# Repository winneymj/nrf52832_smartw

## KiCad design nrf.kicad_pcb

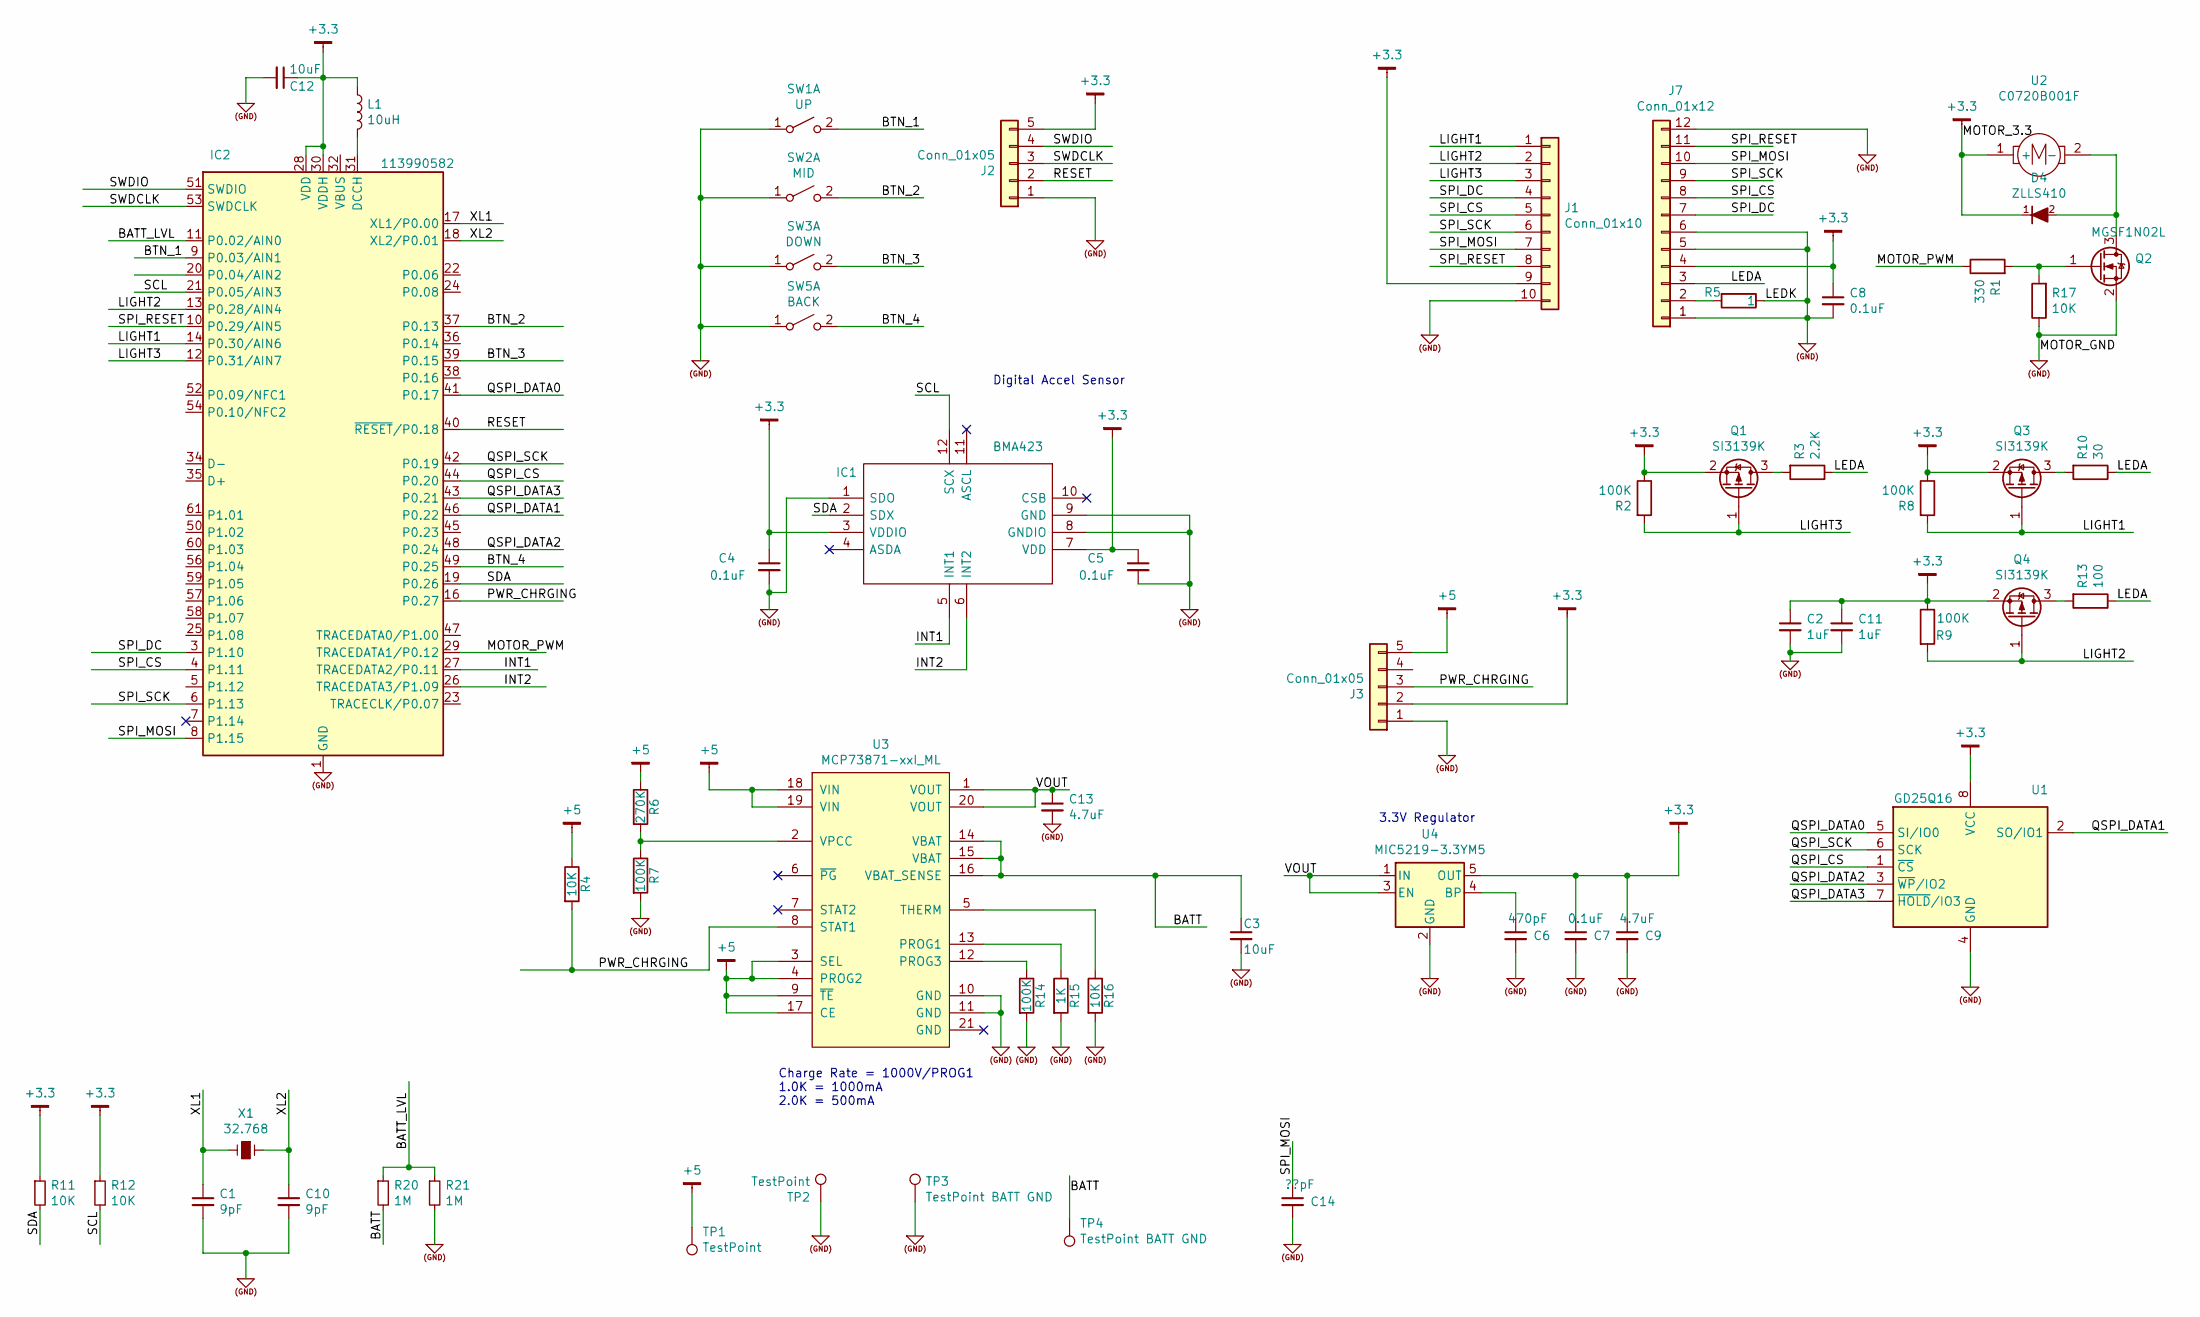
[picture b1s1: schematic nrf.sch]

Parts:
C1, C10: 9pF; C_0603_1608Metric_Pad1.08x0.95mm_HandSolder
C2, C11: 1uF; C_0603_1608Metric_Pad1.08x0.95mm_HandSolder
C3, C12: 10uF; C_0603_1608Metric_Pad1.08x0.95mm_HandSolder
C4, C5, C7, C8: 0.1uF; C_0603_1608Metric_Pad1.08x0.95mm_HandSolder
C6: 470pF; C_0603_1608Metric_Pad1.08x0.95mm_HandSolder
C9, C13: 4.7uF; C_0603_1608Metric_Pad1.08x0.95mm_HandSolder
C14: ??pF; C_0603_1608Metric_Pad1.08x0.95mm_HandSolder
D4: ZLLS410; D_SOD-323_HandSoldering
IC1: BMA423; LGA-12_2x2mm_P0.5mm_small_pad; Mouser Part Number 262-BMA423
IC2: 113990582; Raytac_MDBT50Q; Mouser Part Number 713-113990582
J1: Conn_01x10; Pin_Header_Straight_1x10_Pitch2.54mm
J2: Conn_01x05; Pin_Header_Straight_1x05_Pitch1.27mm
J3: Conn_01x05; Pin_Header_Straight_1x05_Pitch2.54mm
J7: Conn_01x12; FPC_12x0.7mm
L1: 10uH; L_0603_1608Metric_Pad1.05x0.95mm_HandSolder
Q1, Q3, Q4: SI3139K; SOT-723
Q2: MGSF1N02L; SOT-23
R1: 330; R_0603_1608Metric_Pad0.98x0.95mm_HandSolder
R2, R7, R8, R9, R14: 100K; R_0603_1608Metric_Pad0.98x0.95mm_HandSolder
R3: 2.2K; R_0603_1608Metric_Pad0.98x0.95mm_HandSolder
R4, R11, R12, R16, R17: 10K; R_0603_1608Metric_Pad0.98x0.95mm_HandSolder
R5: 1; R_0603_1608Metric_Pad0.98x0.95mm_HandSolder
R6: 270K; R_0603_1608Metric_Pad0.98x0.95mm_HandSolder
R10: 30; R_0603_1608Metric_Pad0.98x0.95mm_HandSolder
R13: 100; R_0603_1608Metric_Pad0.98x0.95mm_HandSolder
R15: 1K; R_0603_1608Metric_Pad0.98x0.95mm_HandSolder
R20, R21: 1M; R_0603_1608Metric_Pad0.98x0.95mm_HandSolder
SW1: UP; Tact_SW_3x6x3.5
SW2: MID; Tact_SW_3x6x3.5
SW3: DOWN; Tact_SW_3x6x3.5
SW5: BACK; Tact_SW_3x6x3.5
TP1, TP2: TestPoint; TestPoint_Pad_D1.5mm
TP3, TP4: TestPoint BATT GND; TestPoint_Pad_2.0x2.0mm
U1: GD25Q16; USON8-4x3
U2: C0720B001F; VIBRATION MOTOR COIN 3V FLEX - C0720B001F
U3: MCP73871-xxI_ML; QFN-20-1EP_4x4mm_Pitch0.5mm; MPN MCP73871-{output}I/ML
U4: MIC5219-3.3YM5; SOT-23-5
X1: 32.768; Crystal_SMD_EuroQuartz_EQ161-2pin_3.2x1.5mm_HandSoldering

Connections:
(GND): C1.2, C2.2, C3.2, C4.2, C5.2, C6.2, C7.2, C8.2, C9.2, C10.2, C11.2, C12.2, C13.2, C14.2, IC1.1 (SDO), IC1.8 (GNDIO), IC1.9 (GND), IC2.1 (GND), IC2.2 (GND), IC2.15 (GND), IC2.33 (GND), IC2.55 (GND), J1.10, J2.1, J3.1, J7.1, J7.5, J7.6, J7.12, Q2.2 (S), R5.1, R7.2, R14.2, R15.2, R16.2, R17.1, R21.2, SW1.1 (A), SW2.1 (A), SW3.1 (A), SW5.1 (A), TP2.1, TP3.1, U1.4 (GND), U3.10 (GND), U3.11 (GND), U4.2 (GND)
+3.3: C2.1, C4.1, C5.1, C7.1, C8.1, C9.1, C11.1, C12.1, D4.1 (K), IC1.3 (VDDIO), IC1.7 (VDD), IC2.28 (VDD), IC2.30 (VDDH), J1.9, J2.5, J3.2, J7.4, L1.1, Q1.2 (S), Q3.2 (S), Q4.2 (S), R2.1, R8.1, R9.1, R11.1, R12.1, U1.8 (VCC), U2.1 (+), U4.5 (OUT)
+5: J3.5, R4.1, R6.1, TP1.1, U3.3 (SEL), U3.4 (PROG2), U3.9 (~TE), U3.17 (CE), U3.18 (VIN), U3.19 (VIN)
/BATT: C3.1, R20.2, TP4.1, U3.14 (VBAT), U3.15 (VBAT), U3.16 (VBAT_SENSE)
/BATT_LVL: IC2.11 (P0.02/AIN0), R20.1, R21.1
/BTN_1: IC2.9 (P0.03/AIN1), SW1.2 (B)
/BTN_2: IC2.37 (P0.13), SW2.2 (B)
/BTN_3: IC2.39 (P0.15), SW3.2 (B)
/BTN_4: IC2.49 (P0.25), SW5.2 (B)
/INT1: IC1.5 (INT1), IC2.27 (TRACEDATA2/P0.11)
/INT2: IC1.6 (INT2), IC2.26 (TRACEDATA3/P1.09)
/LEDA: J7.3, R3.1, R10.1, R13.1
/LIGHT1: IC2.14 (P0.30/AIN6), J1.1, Q3.1 (G), R8.2
/LIGHT2: IC2.13 (P0.28/AIN4), J1.2, Q4.1 (G), R9.2
/LIGHT3: IC2.12 (P0.31/AIN7), J1.3, Q1.1 (G), R2.2
/MOTOR_PWM: IC2.29 (TRACEDATA1/P0.12), R1.1
/PWR_CHRGING: IC2.16 (P0.27), J3.3, R4.2, U3.8 (STAT1)
/QSPI_CS: IC2.44 (P0.20), U1.1 (~CS)
/QSPI_DATA0: IC2.41 (P0.17), U1.5 (SI/IO0)
/QSPI_DATA1: IC2.46 (P0.22), U1.2 (SO/IO1)
/QSPI_DATA2: IC2.48 (P0.24), U1.3 (~WP~/IO2)
/QSPI_DATA3: IC2.43 (P0.21), U1.7 (~HOLD~/IO3)
/QSPI_SCK: IC2.42 (P0.19), U1.6 (SCK)
/RESET: IC2.40 (~RESET~/P0.18), J2.2
/SCL: IC1.12 (SCX), IC2.21 (P0.05/AIN3), R12.2
/SDA: IC1.2 (SDX), IC2.19 (P0.26), R11.2
/SPI_CS: IC2.4 (P1.11), J1.5, J7.8
/SPI_DC: IC2.3 (P1.10), J1.4, J7.7
/SPI_MOSI: C14.1, IC2.8 (P1.15), J1.7, J7.10
/SPI_RESET: IC2.10 (P0.29/AIN5), J1.8, J7.11
/SPI_SCK: IC2.6 (P1.13), J1.6, J7.9
/SWDCLK: IC2.53 (SWDCLK), J2.3
/SWDIO: IC2.51 (SWDIO), J2.4
/VOUT: C13.1, U3.1 (VOUT), U3.20 (VOUT), U4.1 (IN), U4.3 (EN)
/XL1: C1.1, IC2.17 (XL1/P0.00), X1.2
/XL2: C10.1, IC2.18 (XL2/P0.01), X1.1
unnamed: C6.1, U4.4 (BP)
unnamed: D4.2 (A), Q2.3 (D), U2.2 (-)
unnamed: IC2.31 (DCCH), L1.2
unnamed: J7.2, R5.2
unnamed: Q1.3 (D), R3.2
unnamed: Q2.1 (G), R1.2, R17.2
unnamed: Q3.3 (D), R10.2
unnamed: Q4.3 (D), R13.2
unnamed: R6.2, R7.1, U3.2 (VPCC)
unnamed: R14.1, U3.12 (PROG3)
unnamed: R15.1, U3.13 (PROG1)
unnamed: R16.1, U3.5 (THERM)

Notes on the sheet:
Charge Rate = 1000V/PROG1 1.0K = 1000mA 2.0K = 500mA
3.3V Regulator
Digital Accel Sensor

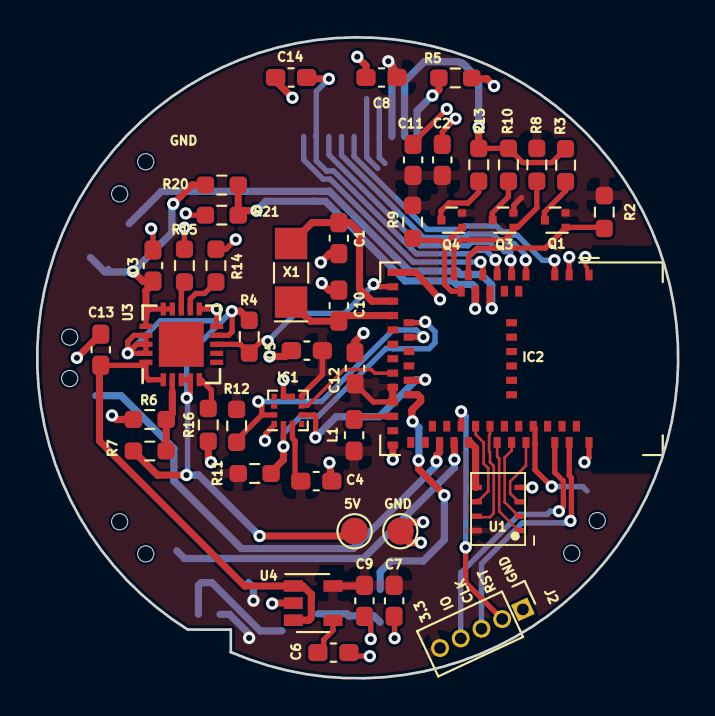
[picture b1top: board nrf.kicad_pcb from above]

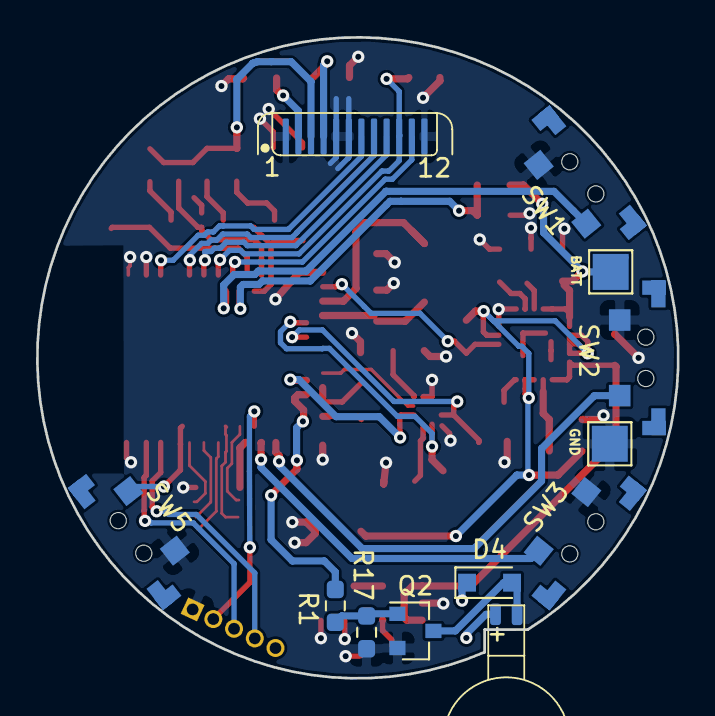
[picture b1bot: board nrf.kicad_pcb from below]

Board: 2 copper layers, 35.6 x 35.6 mm, 56 parts (12 on the bottom side), 48 nets.

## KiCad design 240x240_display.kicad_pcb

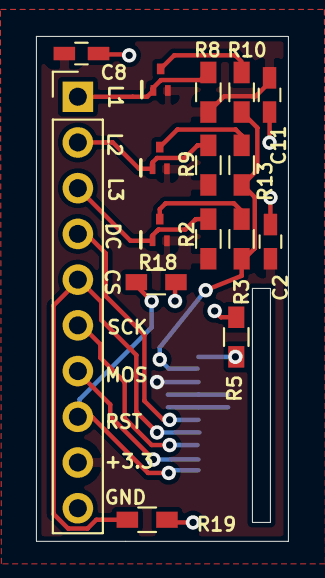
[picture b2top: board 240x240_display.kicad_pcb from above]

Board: 2 copper layers, 14.0 x 28.0 mm, 17 parts (1 on the bottom side), 15 nets.

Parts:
C2, C11: 1uF; C_0603_HandSoldering
C8: 0.1uF; C_0603_HandSoldering
J1: Conn_01x10; Pin_Header_Straight_1x10_Pitch2.54mm
J7: Conn_01x12; FPC_12x0.7mm
Q1, Q3, Q4: SI3139K; SOT-723_Handsoldering
R2, R8, R9: 100K; R_0603_HandSoldering
R3: 2.2K; R_0603_HandSoldering
R5: 1; R_0603_HandSoldering
R10: 30; R_0603_HandSoldering
R13: 100; R_0603_HandSoldering
R18, R19: 10K; R_0603_HandSoldering

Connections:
(GND): C2.2, C8.2, C11.2, J1.10, J7.1, J7.5, J7.6, J7.12, R5.1, R18.2, R19.2
+3.3: C2.1, C8.1, C11.1, J1.9, J7.4, Q1.2, Q3.2, Q4.2, R2.1, R8.1, R9.1
/LEDA: J7.3, R3.1, R10.1, R13.1
/LIGHT1: J1.1, Q3.1, R8.2
/LIGHT2: J1.2, Q4.1, R9.2
/LIGHT3: J1.3, Q1.1, R2.2
/SPI_CS: J1.5, J7.8, R19.1
/SPI_DC: J1.4, J7.7
/SPI_MOSI: J1.7, J7.10
/SPI_RESET: J1.8, J7.11, R18.1
/SPI_SCK: J1.6, J7.9
unnamed: J7.2, R5.2
unnamed: Q1.3, R3.2
unnamed: Q3.3, R10.2
unnamed: Q4.3, R13.2

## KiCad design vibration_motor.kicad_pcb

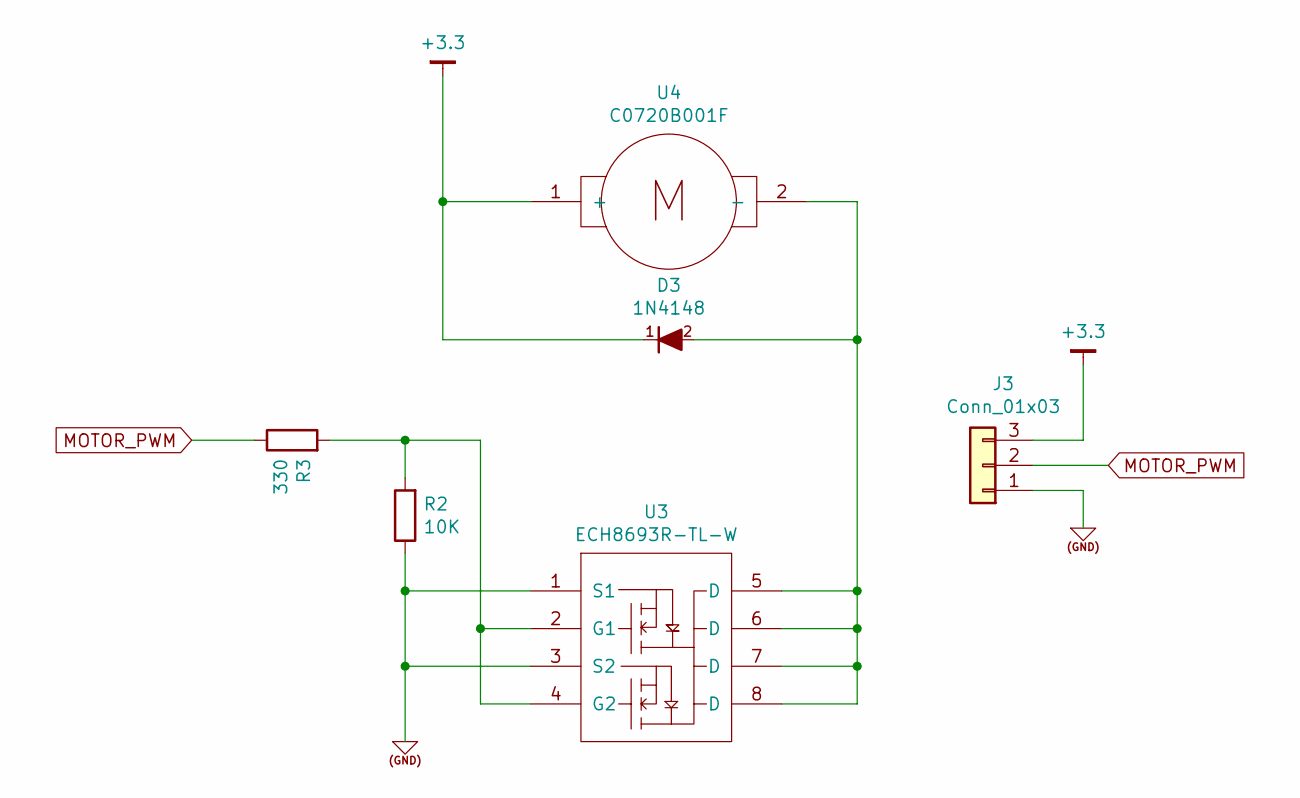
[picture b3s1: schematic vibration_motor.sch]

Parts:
D3: 1N4148; D_SOD-123
J3: Conn_01x03; Pin_Header_Straight_1x03_Pitch2.54mm
R2: 10K; R_0805
R3: 330; R_0805
U3: ECH8693R-TL-W; SOT-28FL
U4: C0720B001F; VIBRATION MOTOR COIN 3V FLEX - C0720B001F

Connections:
(GND): J3.1, R2.1, U3.1 (S1), U3.3 (S2)
+3.3: D3.1 (K), J3.3, U4.1 (+)
MOTOR_PWM: J3.2, R3.1
unnamed: D3.2 (A), U3.5 (D), U3.6 (D), U3.7 (D), U3.8 (D), U4.2 (-)
unnamed: R2.2, R3.2, U3.2 (G1), U3.4 (G2)

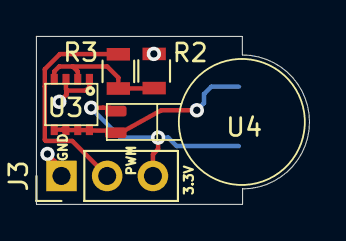
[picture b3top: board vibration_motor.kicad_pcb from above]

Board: 2 copper layers, 15.2 x 9.3 mm, 6 parts (1 on the bottom side), 5 nets.

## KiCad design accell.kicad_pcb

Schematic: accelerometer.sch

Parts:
C4, C5: 100nF; C_0603_HandSoldering
IC1: BMA423; Mouser Part Number 262-BMA423
J4: Conn_01x06; Pin_Header_Straight_1x06_Pitch2.54mm
R11, R12: 10K; R_0603_HandSoldering

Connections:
(GND): C4.2, C5.2, IC1.1 (SDO), IC1.8 (GNDIO), IC1.9 (GND), J4.6
+3.3: C4.1, C5.1, IC1.3 (VDDIO), IC1.7 (VDD), J4.1, R11.1, R12.1
I2C_SCL: IC1.12 (SCX), J4.3, R11.2
I2C_SDA: IC1.2 (SDX), J4.2, R12.2
XL_INT_1: IC1.5 (INT1), J4.4
XL_INT_2: IC1.6 (INT2), J4.5

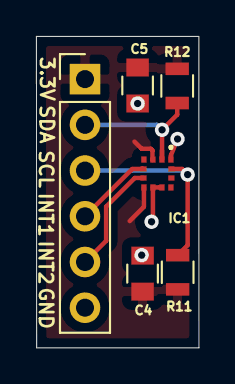
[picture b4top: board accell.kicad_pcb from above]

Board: 2 copper layers, 9.0 x 17.3 mm, 6 parts (0 on the bottom side), 6 nets.

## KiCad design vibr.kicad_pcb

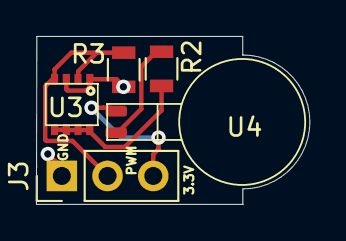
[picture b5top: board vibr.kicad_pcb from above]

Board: 2 copper layers, 15.2 x 9.3 mm, 5 parts (0 on the bottom side), 5 nets.

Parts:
J3: Conn_01x03; Pin_Header_Straight_1x03_Pitch2.54mm
R2: 10K; R_0805
R3: 330; R_0805
U3: ECH8693R-TL-W; SOT-28FL
U4: C0720B001F; VIBRATION MOTOR COIN 3V FLEX - C0720B001F

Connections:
(GND): J3.1, R2.1, U3.1, U3.3
+3.3: J3.3, U4.1
MOTOR_PWM: J3.2, R2.2, U3.2, U3.4
unnamed: R3.1, U3.5, U3.6, U3.7, U3.8
unnamed: R3.2, U4.2

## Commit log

2019-06-20 More power setup
2019-06-22 Connectors
2019-06-23 Layout power
2019-06-24 More power connections
2019-06-25 More PCB setup
2019-07-03 New PCB's
2019-07-04 accelerometer
2019-08-04 Rework and rename parts
2019-10-05 New Power_Management from Pin64 schematic. Much less parts
2019-10-14 Implement 240x240 IPS display
2019-10-16 Power board PCB
2019-10-17 Build power board
2019-10-18 More power board layout
2019-10-20 v.01 power board PCB
2019-10-27 Circular Display
2019-10-28 update for display footprint
2019-11-05 update for power footprint
2020-05-12 Initial
2020-05-12 see what happens
2020-05-14 Update for accel
2020-05-17 Move power from sub sheet
2020-05-18 Layout board
2020-10-25 More layout changes
2020-11-01 Board Update
2020-11-03 Change resistors to 0603 imperial
2020-11-25 Update footprints
2020-11-30 Update GND connections from under pads
2021-01-30 Board updates
